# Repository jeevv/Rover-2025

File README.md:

# Astra Rover 2025
Every year Astra Robotics participates in a number of rover competitions. This repo is way to store all of the code associated with the rover project in the form of STM32CUBEIDE projects or ROS nodes. It also serves as a way to issue general instructions, track common bugs, raise issues, and keep track of which team is doing what. The idea is to allow anyone with sufficient technical expertise to join the project and start contributing using this repo.

## Embedded Subsystem
### General Instructions
- Try to maintain a single version of STM32CUDEIDE, it gets cranky when you open projects made with an older version of the IDE.
- Do go through the FreeRTOS API and make sure to understand the basic concepts behind what a scheduler is, what kind of advantages an RTOS offers, and so on.
- Install MicroROS throught the GitHub repo only. Follow the instructions, make sure to check for the humble branch to match the version of ROS2.
### Current Task
- Start using the RTOS features on the current version of the rover code

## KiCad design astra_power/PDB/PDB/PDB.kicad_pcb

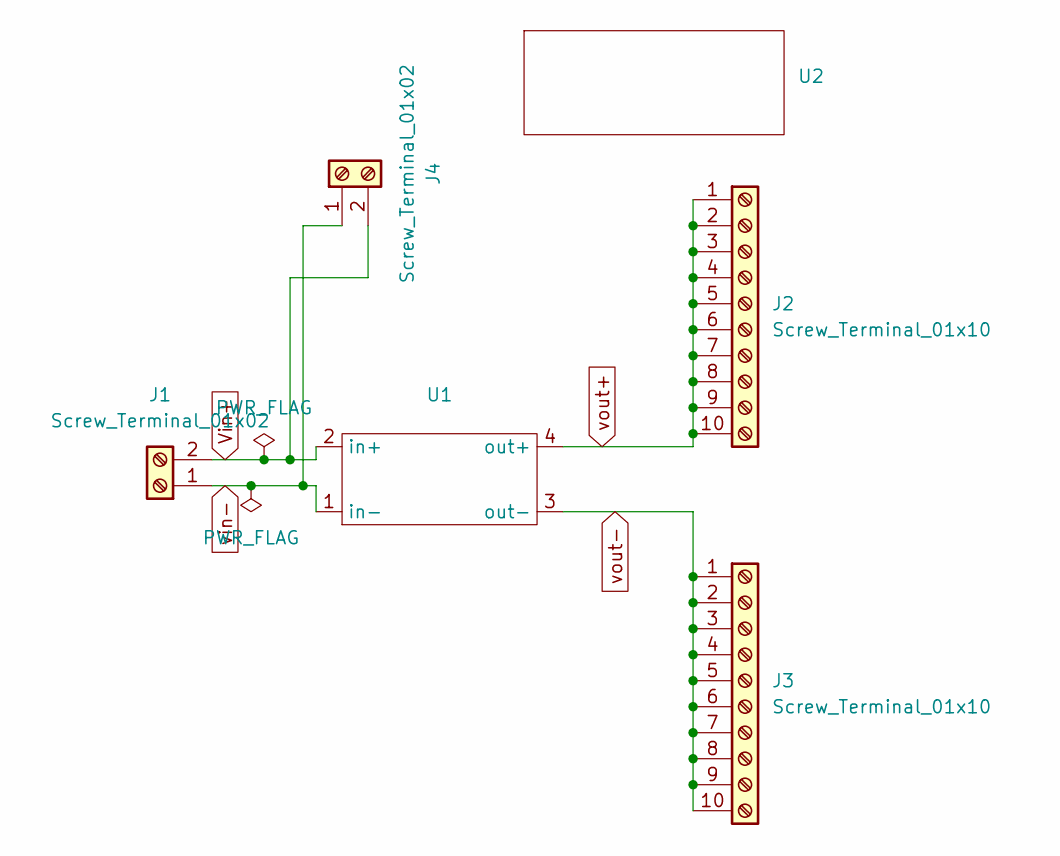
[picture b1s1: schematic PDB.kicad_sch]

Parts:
J1, J4: Screw_Terminal_01x02; TerminalBlock_Xinya_XY308-2.54-2P_1x02_P2.54mm_Horizontal
J2, J3: Screw_Terminal_01x10; TerminalBlock_Xinya_XY308-2.54-10P_1x10_P2.54mm_Horizontal
U1: LM2596-dev_board
U2: stps_boost

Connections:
Vin+: J1.2, J4.2, U1.2 (in+)
vin-: J1.1, J4.1, U1.1 (in-)
vout+: J2.1, J2.2, J2.3, J2.4, J2.5, J2.6, J2.7, J2.8, J2.9, J2.10, U1.4 (out+)
vout-: J3.1, J3.2, J3.3, J3.4, J3.5, J3.6, J3.7, J3.8, J3.9, J3.10, U1.3 (out-)

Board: 2 copper layers, 6 parts (0 on the bottom side), 4 nets, no tracks yet.

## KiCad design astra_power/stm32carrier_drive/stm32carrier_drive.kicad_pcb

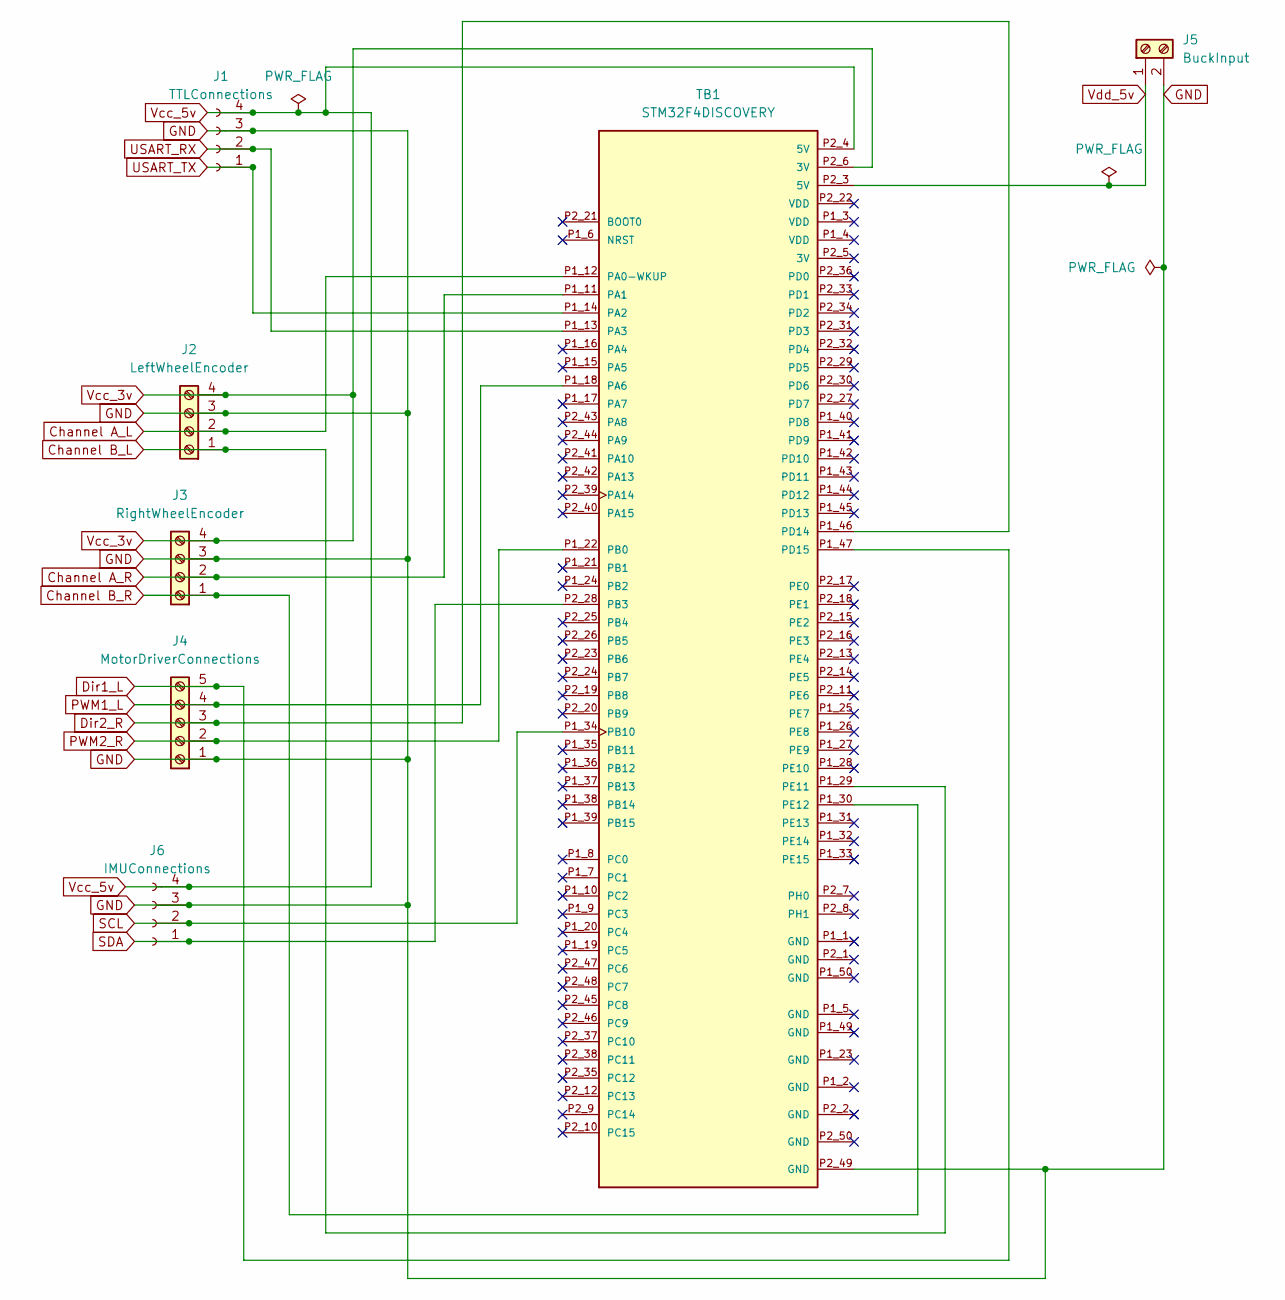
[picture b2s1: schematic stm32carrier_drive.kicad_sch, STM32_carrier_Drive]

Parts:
J1: TTLConnections; PinSocket_1x04_P1.00mm_Vertical_SMD_Pin1Left
J2: LeftWheelEncoder; TerminalBlock_Xinya_XY308-2.54-4P_1x04_P2.54mm_Horizontal
J3: RightWheelEncoder; TerminalBlock_Xinya_XY308-2.54-4P_1x04_P2.54mm_Horizontal
J4: MotorDriverConnections; TerminalBlock_Xinya_XY308-2.54-5P_1x05_P2.54mm_Horizontal
J5: BuckInput; TerminalBlock_Xinya_XY308-2.54-2P_1x02_P2.54mm_Horizontal
J6: IMUConnections; PinSocket_1x04_P1.00mm_Vertical_SMD_Pin1Left
TB1: STM32F4DISCOVERY; MODULE_STM32F4DISCOVERY; PARTREV 6

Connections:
Channel A_L: J2.2, TB1.P1_12 (PA0-WKUP)
Channel A_R: J3.2, TB1.P1_11 (PA1)
Channel B_L: J2.1, TB1.P1_29 (PE11)
Channel B_R: J3.1, TB1.P1_30 (PE12)
Dir1_L: J4.5, TB1.P1_47 (PD15)
Dir2_R: J4.3, TB1.P1_46 (PD14)
GND: J1.3, J2.3, J3.3, J4.1, J5.2, J6.3, TB1.P2_49 (GND)
PWM1_L: J4.4, TB1.P1_18 (PA6)
PWM2_R: J4.2, TB1.P1_22 (PB0)
SCL: J6.2, TB1.P1_34 (PB10)
SDA: J6.1, TB1.P2_28 (PB3)
USART_RX: J1.2, TB1.P1_13 (PA3)
USART_TX: J1.1, TB1.P1_14 (PA2)
Vcc_3v: J2.4, J3.4, TB1.P2_6 (3V)
Vcc_5v: J1.4, J6.4, TB1.P2_4 (5V)
Vdd_5v: J5.1, TB1.P2_3 (5V)

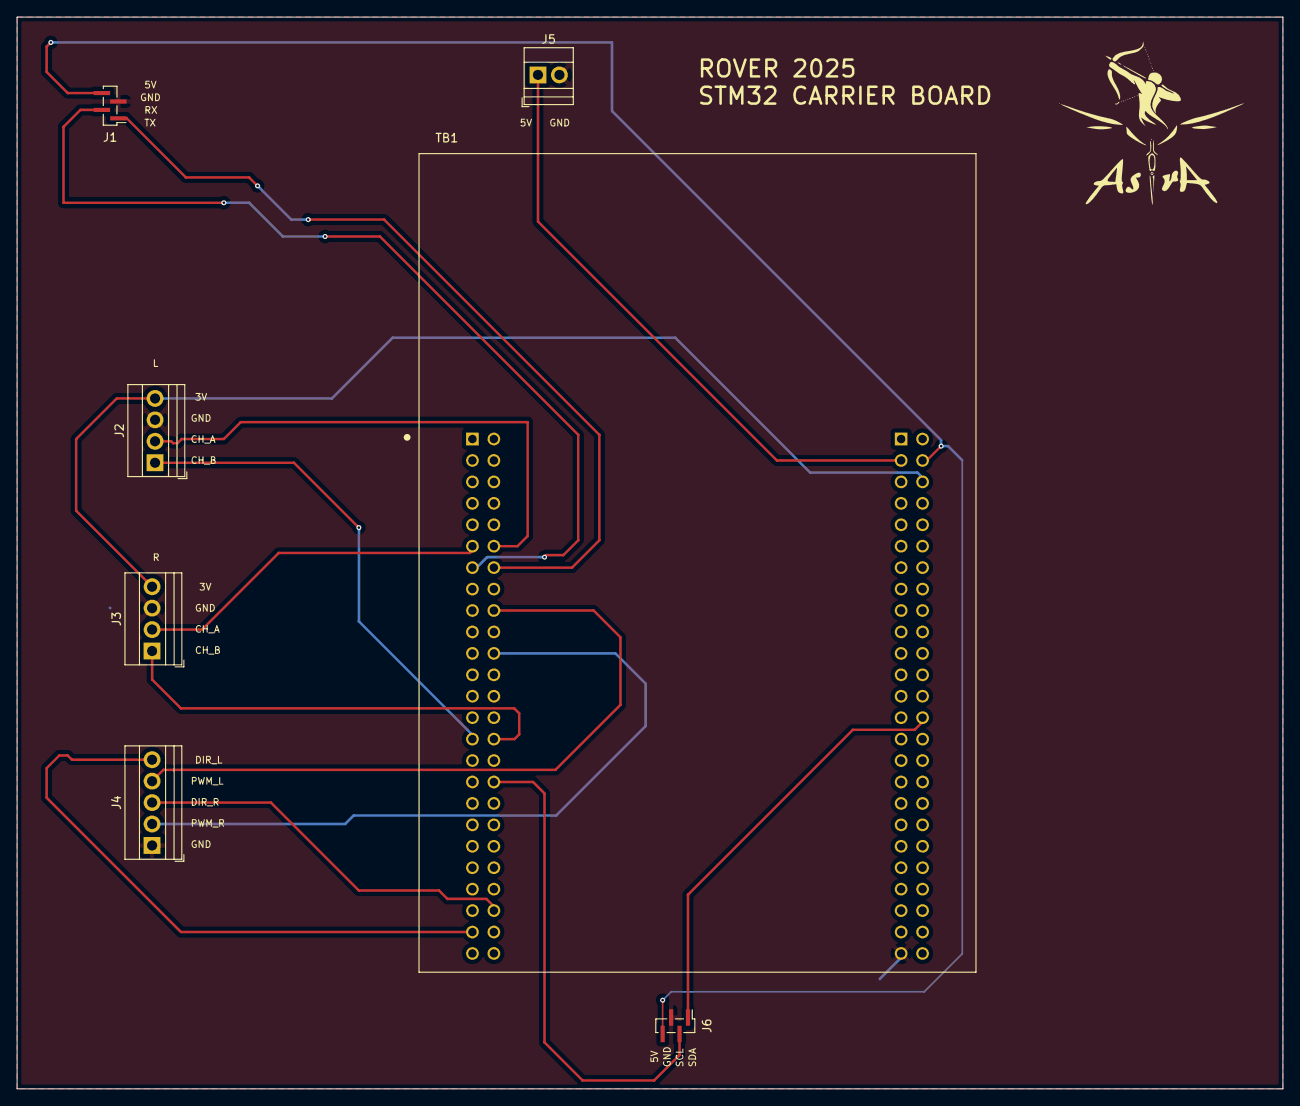
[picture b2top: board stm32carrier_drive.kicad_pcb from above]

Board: 2 copper layers, 150.0 x 127.0 mm, 7 parts (0 on the bottom side), 16 nets.

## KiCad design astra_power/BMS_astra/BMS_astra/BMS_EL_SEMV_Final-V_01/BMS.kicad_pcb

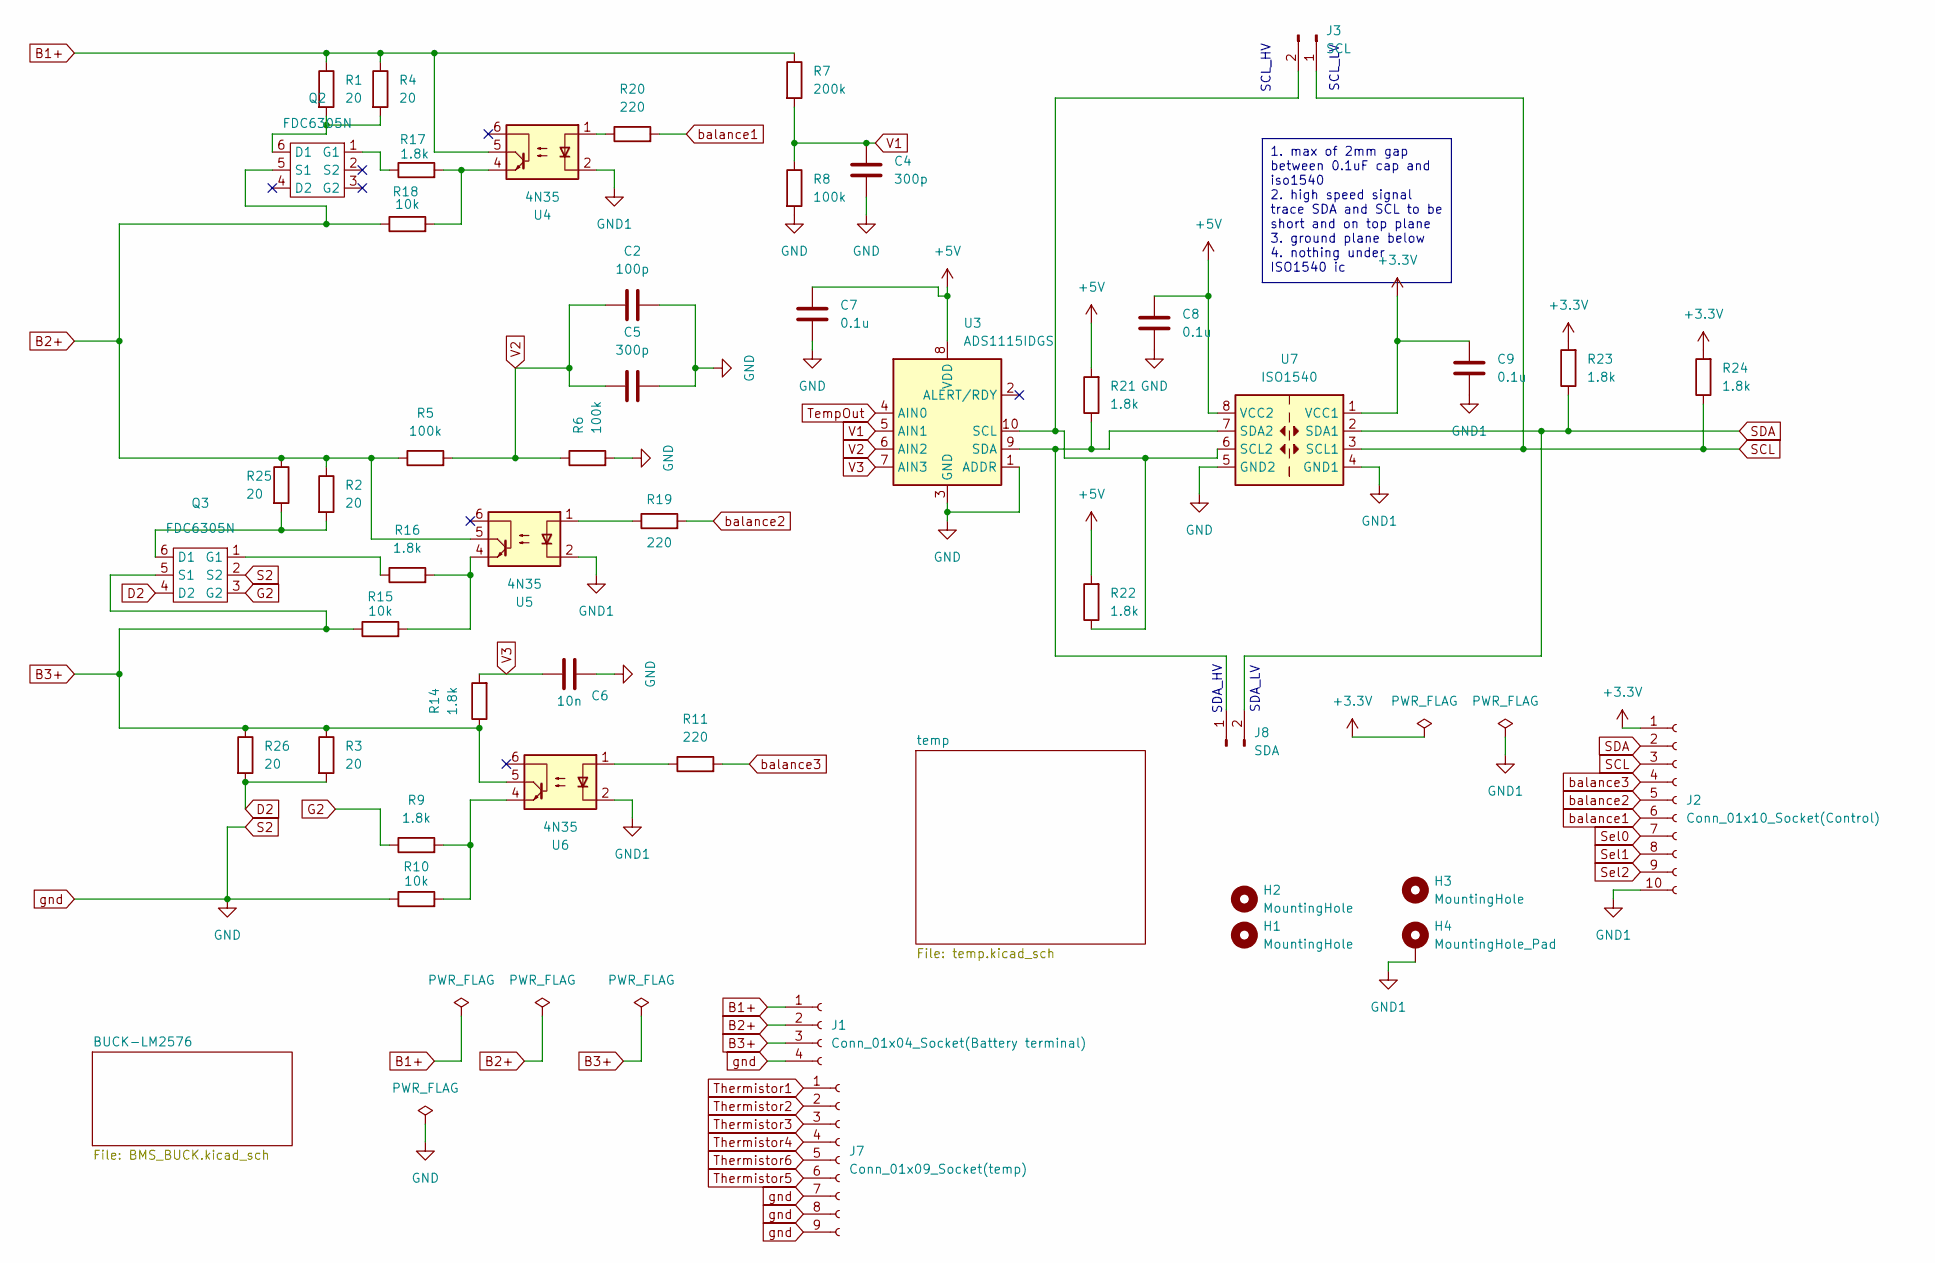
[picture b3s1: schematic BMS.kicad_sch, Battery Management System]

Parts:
C2: 100p; C_0805_2012Metric_Pad1.18x1.45mm_HandSolder
C4, C5: 300p; C_0805_2012Metric_Pad1.18x1.45mm_HandSolder
C6: 10n; C_0603_1608Metric_Pad1.08x0.95mm_HandSolder
C7, C8, C9: 0.1u; C_0603_1608Metric_Pad1.08x0.95mm_HandSolder
H1, H2, H3: MountingHole; MountingHole_3.2mm_M3
H4: MountingHole_Pad; MountingHole_3.2mm_M3_DIN965_Pad
J1: Conn_01x04_Socket(Battery terminal); JST_XH_S4B-XH-A_1x04_P2.50mm_Horizontal
J2: Conn_01x10_Socket(Control); JST_XH_S10B-XH-A-1_1x10_P2.50mm_Horizontal
J3: SCL; PinHeader_1x02_P2.54mm_Vertical
J7: Conn_01x09_Socket(temp); JST_XH_S9B-XH-A-1_1x09_P2.50mm_Horizontal
J8: SDA; PinHeader_1x02_P2.54mm_Vertical
Q2, Q3: FDC6305N; SuperSOT-6
R1, R2, R3, R4, R25, R26: 20; R_2512_6332Metric_Pad1.40x3.35mm_HandSolder
R5, R6, R8: 100k; R_0805_2012Metric_Pad1.20x1.40mm_HandSolder
R7: 200k; R_0805_2012Metric_Pad1.20x1.40mm_HandSolder
R9, R14, R16, R17, R21, R22, R23, R24: 1.8k; R_0805_2012Metric_Pad1.20x1.40mm_HandSolder
R10, R15, R18: 10k; R_0805_2012Metric_Pad1.20x1.40mm_HandSolder
R11, R19, R20: 220; R_0805_2012Metric_Pad1.20x1.40mm_HandSolder
U3: ADS1115IDGS; TSSOP-10_3x3mm_P0.5mm
U4, U5, U6: 4N35; DIP-6_W7.62mm
U7: ISO1540; SOIC-8_3.9x4.9mm_P1.27mm

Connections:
+3.3V: C9.1, J2.1, R23.2, R24.2, U7.1 (VCC1)
+5V: C7.1, C8.1, R21.2, R22.2, U3.8 (VDD), U7.8 (VCC2); also elsewhere on the board
A0: J7.1; also elsewhere on the board
A1: J7.2; also elsewhere on the board
A2: J7.3; also elsewhere on the board
A3: J7.4; also elsewhere on the board
A4: J7.6; also elsewhere on the board
A5: J7.5; also elsewhere on the board
B1+: J1.1, R1.1, R4.1, R7.1, U4.5; also elsewhere on the board
B2+: J1.2, Q2.5 (S1), R2.1, R5.1, R18.1, R25.1, U5.5
B3+: J1.3, Q3.5 (S1), R3.1, R14.1, R15.1, R26.1, U6.5
D2: Q3.4 (D2), R3.2, R26.2
G2: Q3.3 (G2), R9.1
GND1: C9.2, H4.1, J2.10, U4.2, U5.2, U6.2, U7.4 (GND1); also elsewhere on the board
unnamed: J3.2, R22.1, U3.10 (SCL), U7.6 (SCL2)
unnamed: J8.1, R21.1, U3.9 (SDA), U7.7 (SDA2)
unnamed: Q2.6 (D1), R1.2, R4.2
unnamed: Q2.1 (G1), R17.1
unnamed: Q3.6 (D1), R2.2, R25.2
unnamed: Q3.1 (G1), R16.1
unnamed: R9.2, R10.2, U6.4
unnamed: R11.1, U6.1
unnamed: R15.2, R16.2, U5.4
unnamed: R17.2, R18.2, U4.4
unnamed: R19.1, U5.1
unnamed: R20.1, U4.1
S2: C2.2, C4.2, C5.2, C6.2, C7.2, C8.2, J1.4, J7.7, J7.8, J7.9, Q3.2 (S2), R6.2, R8.2, R10.1, U3.1 (ADDR), U3.3 (GND), U7.5 (GND2); also elsewhere on the board
SCL: J2.3, J3.1, R24.1, U7.3 (SCL1)
SDA: J2.2, J8.2, R23.1, U7.2 (SDA1)
Sel0: J2.7; also elsewhere on the board
Sel1: J2.8; also elsewhere on the board
Sel2: J2.9; also elsewhere on the board
TempOut: U3.4 (AIN0); also elsewhere on the board
V1: C4.1, R7.2, R8.1, U3.5 (AIN1)
V2: C2.1, C5.1, R5.2, R6.1, U3.6 (AIN2)
V3: C6.1, R14.2, U3.7 (AIN3)
balance1: J2.6, R20.2
balance2: J2.5, R19.2
balance3: J2.4, R11.2

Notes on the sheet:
1. max of 2mm gap between 0.1uF cap and iso1540 2. high speed signal trace SDA and SCL to be short and on top plane 3. ground plane below 4. nothing under ISO1540 ic
SDA_HV
SCL_LV
SDA_LV
SCL_HV

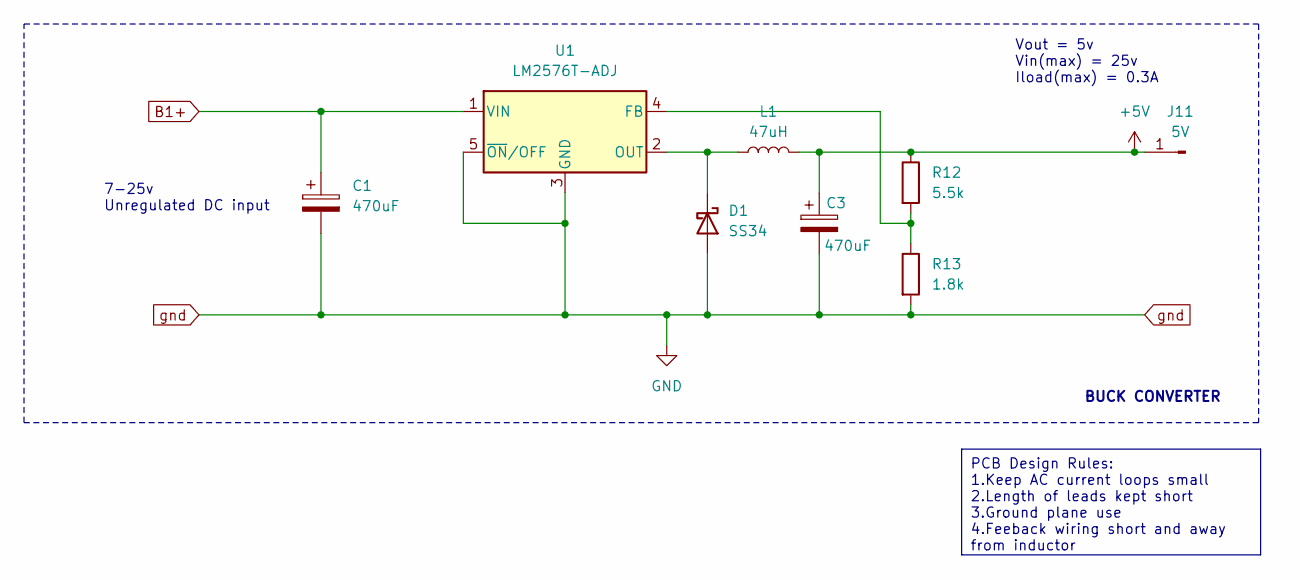
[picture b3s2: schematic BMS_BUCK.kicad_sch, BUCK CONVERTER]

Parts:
C1, C3: 470uF; CP_Elec_10x10.5
D1: SS34; SOD_34FA_ONS
J11: 5V; PinHeader_1x01_P2.54mm_Vertical
L1: 47uH; L_10.4x10.4_H4.8
R12: 5.5k; R_0805_2012Metric_Pad1.20x1.40mm_HandSolder
R13: 1.8k; R_0805_2012Metric_Pad1.20x1.40mm_HandSolder
U1: LM2576T-ADJ; TO-263-5_TabPin3

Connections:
+5V: C3.1, J11.1, L1.2, R12.1; also elsewhere on the board
B1+: C1.1, U1.1 (VIN); also elsewhere on the board
unnamed: D1.1 (K), L1.1, U1.2 (OUT)
unnamed: R12.2, R13.1, U1.4 (FB)
S2: C1.2, C3.2, D1.2 (A), R13.2, U1.3 (GND), U1.5 (~ON/OFF); also elsewhere on the board

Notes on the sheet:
PCB Design Rules: 1.Keep AC current loops small 2.Length of leads kept short 3.Ground plane use 4.Feeback wiring short and away from inductor
7-25v Unregulated DC input
Vout = 5v Vin(max) = 25v Iload(max) = 0.3A
BUCK CONVERTER

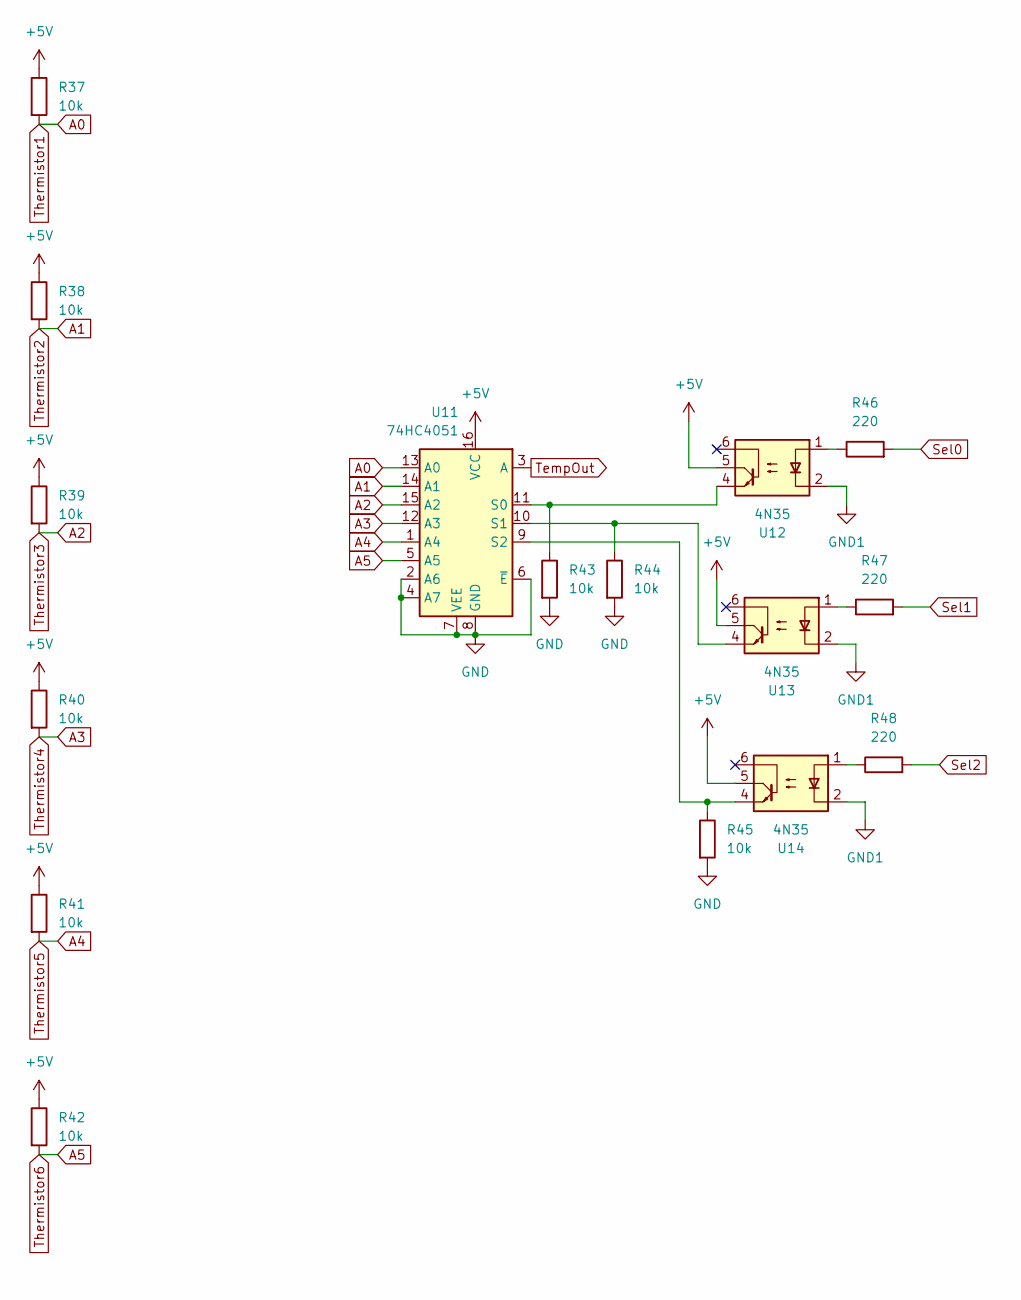
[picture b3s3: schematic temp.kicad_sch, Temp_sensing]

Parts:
R37, R38, R39, R40, R41, R42, R43, R44, R45: 10k; R_0805_2012Metric_Pad1.20x1.40mm_HandSolder
R46, R47, R48: 220; R_0805_2012Metric_Pad1.20x1.40mm_HandSolder
U11: 74HC4051; SOP-16_3.9x9.9mm_P1.27mm
U12, U13, U14: 4N35; DIP-6_W7.62mm

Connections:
+5V: R37.1, R38.1, R39.1, R40.1, R41.1, R42.1, U11.16 (VCC), U12.5, U13.5, U14.5; also elsewhere on the board
A0: R37.2, U11.13 (A0); also elsewhere on the board
A1: R38.2, U11.14 (A1); also elsewhere on the board
A2: R39.2, U11.15 (A2); also elsewhere on the board
A3: R40.2, U11.12 (A3); also elsewhere on the board
A4: R41.2, U11.1 (A4); also elsewhere on the board
A5: R42.2, U11.5 (A5); also elsewhere on the board
GND1: U12.2, U13.2, U14.2; also elsewhere on the board
unnamed: R46.1, U12.1
unnamed: R47.1, U13.1
unnamed: R48.1, U14.1
unnamed: R43.1, U11.11 (S0), U12.4
unnamed: R44.1, U11.10 (S1), U13.4
unnamed: R45.1, U11.9 (S2), U14.4
S2: R43.2, R44.2, R45.2, U11.2 (A6), U11.4 (A7), U11.6 (~E), U11.7 (VEE), U11.8 (GND); also elsewhere on the board
Sel0: R46.2; also elsewhere on the board
Sel1: R47.2; also elsewhere on the board
Sel2: R48.2; also elsewhere on the board
TempOut: U11.3 (A); also elsewhere on the board

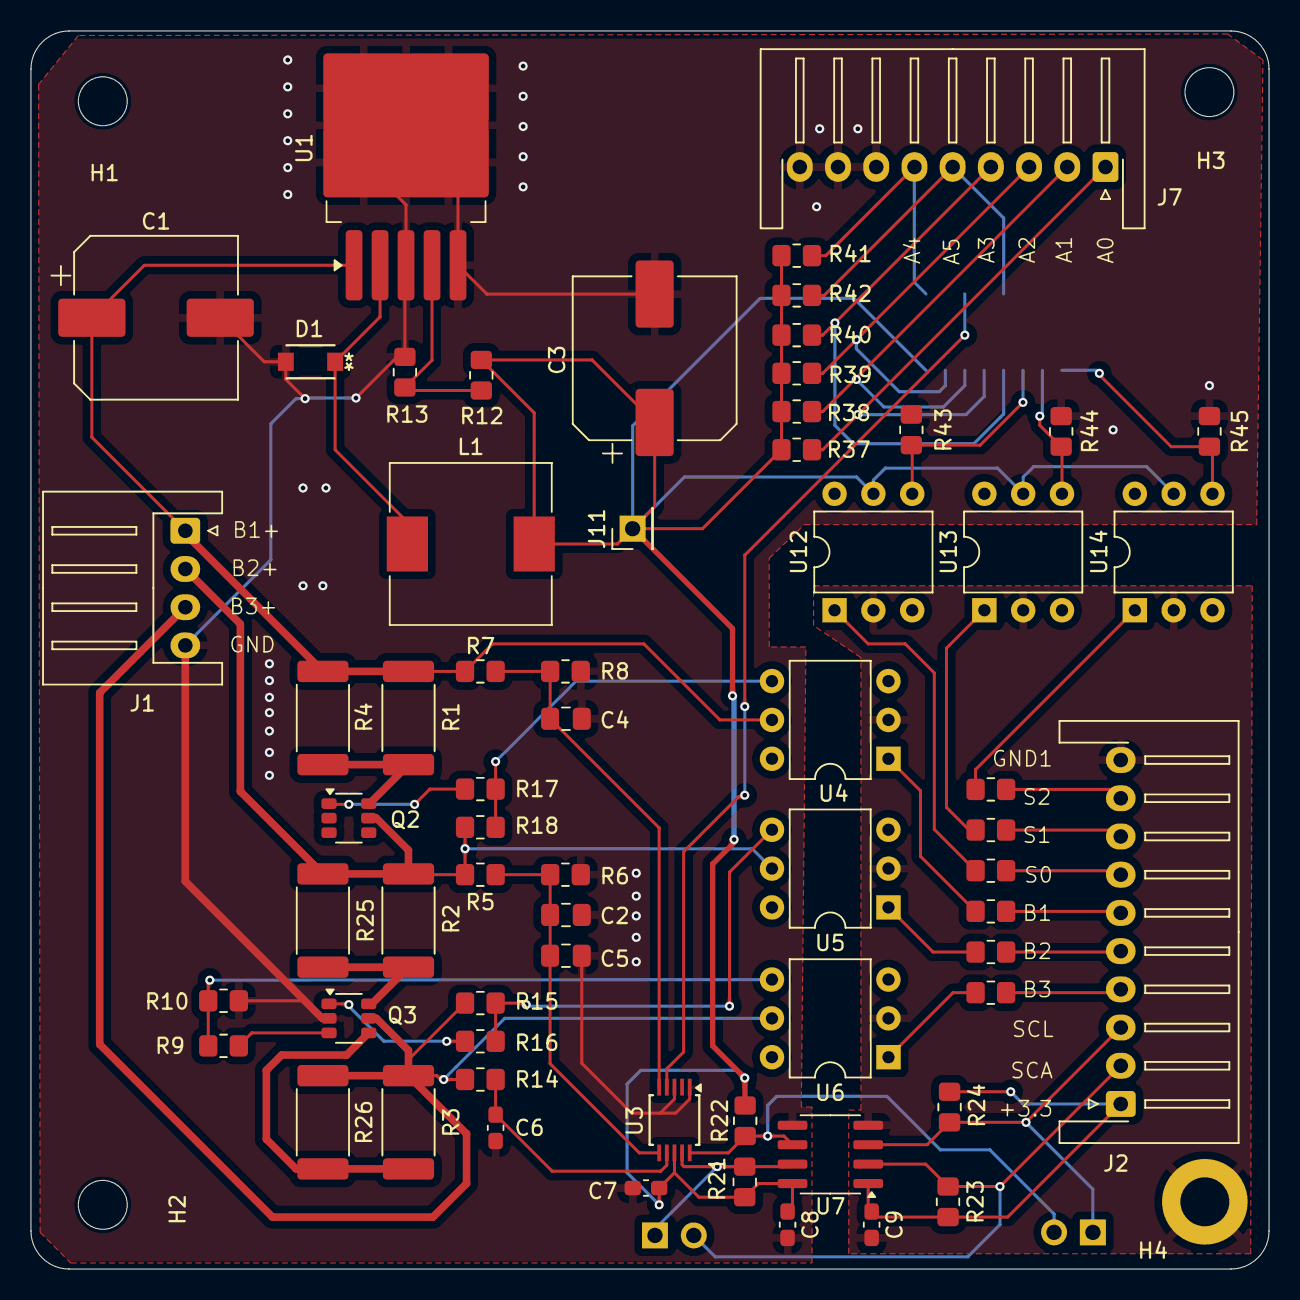
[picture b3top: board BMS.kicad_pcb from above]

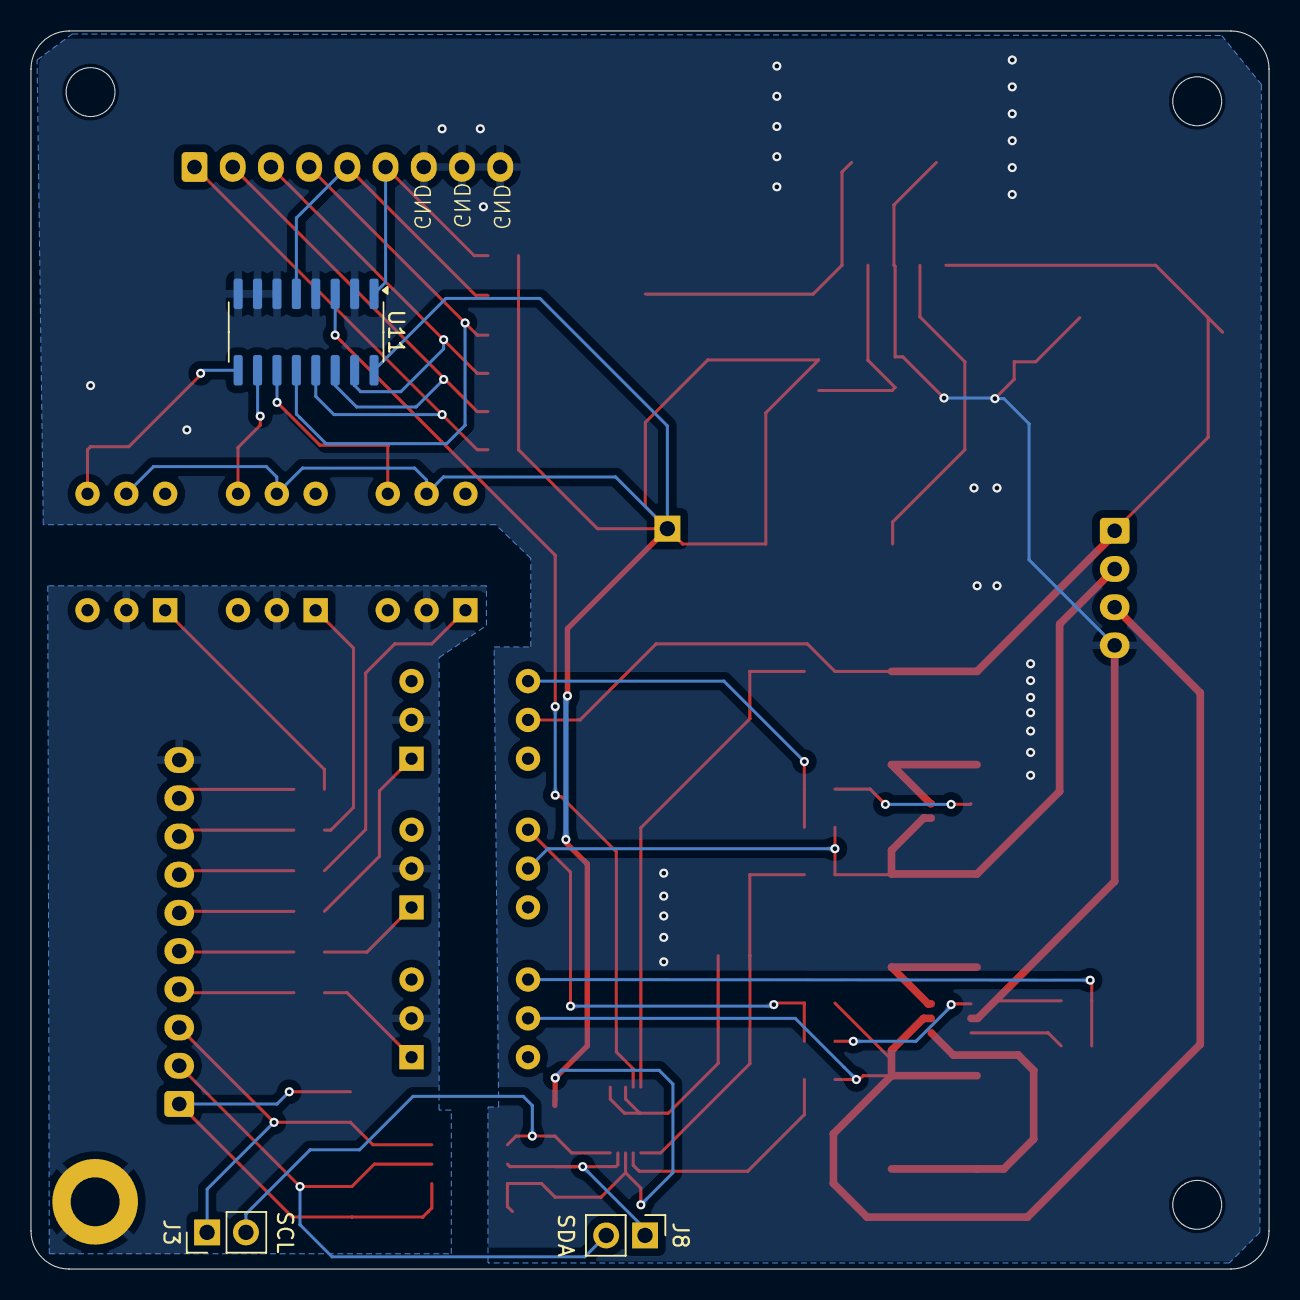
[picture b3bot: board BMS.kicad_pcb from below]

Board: 2 copper layers, 81.0 x 81.0 mm, 71 parts (3 on the bottom side), 47 nets.

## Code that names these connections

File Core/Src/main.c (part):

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	LeftMotorSpeed = (int)(LeftWheelVelocity/WheelRadius) * 60/6.2831;            //w of motor in rpm
	RightMotorSpeed = (int)(RightWheelVelocity/WheelRadius) * 60/6.2831;

	//PWM2 Right motor PA6
	//PWM1 Right motor PA7
	//PWM2 Left motor PB1
	//PWM1 Left motor PB0

	if (LeftMotorSpeed>=0 && LeftMotorSpeed<=1000 && RightMotorSpeed>=0 && RightMotorSpeed<=1000)	//front
	{
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
void HAL_GPIO_EXTI_Callback(uint16_t GPIO_Pin)
{
	if (GPIO_Pin == GPIO_PIN_0)					//PA0 LeftWheelEncoderChannelA  PE11 LeftWheelEncoderChannelB
	{
//		LeftWheelEncoder++;
		if (HAL_GPIO_ReadPin(GPIOE, GPIO_PIN_11) == 1) LeftWheelEncoder++;
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
//		switch(HAL_GPIO_ReadPin(GPIOE, GPIO_PIN_11))
	}
	else if (GPIO_Pin == GPIO_PIN_1)					//PA1 RightWheelEncoderChannelA  PE12 RightWheelEncoderChannelB
	{
//		RightWheelEncoder++;
		if (HAL_GPIO_ReadPin(GPIOE, GPIO_PIN_12) == 0) RightWheelEncoder++;
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  /*Configure GPIO pin Output Level */
  HAL_GPIO_WritePin(GPIOD, GPIO_PIN_14|GPIO_PIN_15, GPIO_PIN_RESET);

  /*Configure GPIO pins : PA0 PA1 */
  GPIO_InitStruct.Pin = GPIO_PIN_0|GPIO_PIN_1;
  GPIO_InitStruct.Mode = GPIO_MODE_IT_RISING;
  GPIO_InitStruct.Pull = GPIO_NOPULL;
  HAL_GPIO_Init(GPIOA, &GPIO_InitStruct);

  /*Configure GPIO pins : PE11 PE12 */
  GPIO_InitStruct.Pin = GPIO_PIN_11|GPIO_PIN_12;
  GPIO_InitStruct.Mode = GPIO_MODE_INPUT;
  GPIO_InitStruct.Pull = GPIO_NOPULL;
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  GPIO_InitStruct.Pull = GPIO_NOPULL;
  HAL_GPIO_Init(GPIOD, &GPIO_InitStruct);

  /*Configure GPIO pins : PD14 PD15 */
  GPIO_InitStruct.Pin = GPIO_PIN_14|GPIO_PIN_15;
  GPIO_InitStruct.Mode = GPIO_MODE_OUTPUT_PP;
  GPIO_InitStruct.Pull = GPIO_NOPULL;
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
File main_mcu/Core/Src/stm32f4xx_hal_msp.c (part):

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
    __HAL_RCC_GPIOB_CLK_ENABLE();
    /**I2C2 GPIO Configuration
    PB10     ------> I2C2_SCL
    PB3     ------> I2C2_SDA
    */
    GPIO_InitStruct.Pin = GPIO_PIN_10;
    GPIO_InitStruct.Mode = GPIO_MODE_AF_OD;
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    __HAL_RCC_I2C2_CLK_DISABLE();

    /**I2C2 GPIO Configuration
    PB10     ------> I2C2_SCL
    PB3     ------> I2C2_SDA
    */
    HAL_GPIO_DeInit(GPIOB, GPIO_PIN_10);

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    __HAL_RCC_GPIOA_CLK_ENABLE();
    __HAL_RCC_GPIOB_CLK_ENABLE();
    /**TIM3 GPIO Configuration
    PA6     ------> TIM3_CH1
    PA7     ------> TIM3_CH2
    PB0     ------> TIM3_CH3
    PB1     ------> TIM3_CH4
    */
    GPIO_InitStruct.Pin = GPIO_PIN_6|GPIO_PIN_7;
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
    __HAL_RCC_GPIOA_CLK_ENABLE();
    /**USART2 GPIO Configuration
    PA2     ------> USART2_TX
    PA3     ------> USART2_RX
    */
    GPIO_InitStruct.Pin = GPIO_PIN_2|GPIO_PIN_3;
    GPIO_InitStruct.Mode = GPIO_MODE_AF_PP;
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    __HAL_RCC_USART2_CLK_DISABLE();

    /**USART2 GPIO Configuration
    PA2     ------> USART2_TX
    PA3     ------> USART2_RX
    */
    HAL_GPIO_DeInit(GPIOA, GPIO_PIN_2|GPIO_PIN_3);

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
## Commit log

2024-11-24 Reorganised the repo
2024-11-24 more reorganisation
2024-11-24 added a README
2024-11-24 spelling mistake
2024-11-30 final
2024-12-01 changed code generation
2024-12-03 Fixed code generator fuckup
2024-12-03 fixed building
2024-12-03 added new mpu code
2024-12-07 completed freertos integration
2024-12-07 reorganising the files
2024-12-14 created pid header and source files
2024-12-15 added pid features
2025-01-18 added some power files
2025-01-18 final carrier board uploaded
2025-02-16 uploaded PDB

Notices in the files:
Core/Src/main.c:
Copyright (c) 2024 STMicroelectronics.
All rights reserved.
This software is licensed under terms that can be found in the LICENSE file
